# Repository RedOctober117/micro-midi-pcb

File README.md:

This repository contains the PCB for [micro-midi](https://github.com/RedOctober117/micro-midi).

## Dependencies
 - [scottokeebs](https://github.com/joe-scotto/scottokeebs)

## Examples

Outdated:

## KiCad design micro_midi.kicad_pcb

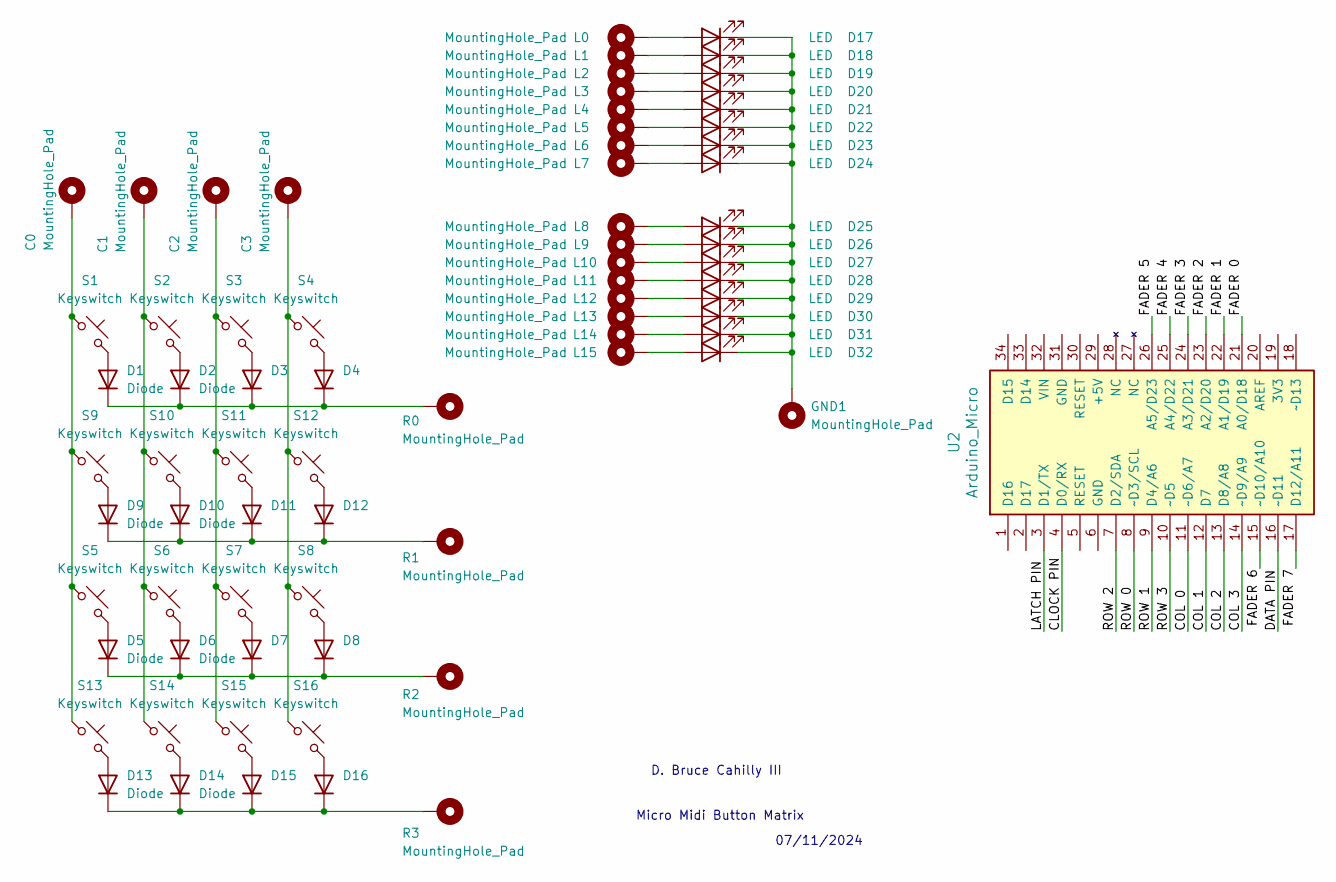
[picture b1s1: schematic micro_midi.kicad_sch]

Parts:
C0, C1, C2, C3: MountingHole_Pad; THROUGH HOLE PAD 1.7MM HOLE 3.0MM PAD
D1, D2, D3, D4, D5, D6, D7, D8, D9, D10, D11, D12, D13, D14, D15, D16: Diode; Diode_DO-35
D17, D18, D19, D20, D21, D22, D23, D24, D25, D26, D27, D28, D29, D30, D31, D32: LED; LED_D3.0mm
GND1: MountingHole_Pad; THROUGH HOLE PAD 1.7MM HOLE 3.0MM PAD
L0, L1, L2, L3, L4, L5, L6, L7, L8, L9, L10, L11, L12, L13, L14, L15: MountingHole_Pad; THROUGH HOLE PAD 1.7MM HOLE 3.0MM PAD
R0, R1, R2, R3: MountingHole_Pad; THROUGH HOLE PAD 1.7MM HOLE 3.0MM PAD
S1, S2, S3, S4, S5, S6, S7, S8, S9, S10, S11, S12, S13, S14, S15, S16: Keyswitch; MX_PCB_1.00u
U2: Arduino_Micro

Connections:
unnamed: C0.1, S1.1, S5.1, S9.1, S13.1
unnamed: C1.1, S2.1, S6.1, S10.1, S14.1
unnamed: C2.1, S3.1, S7.1, S11.1, S15.1
unnamed: C3.1, S4.1, S8.1, S12.1, S16.1
unnamed: D1.2 (A), S1.2
unnamed: D1.1 (K), D2.1 (K), D3.1 (K), D4.1 (K), R0.1
unnamed: D2.2 (A), S2.2
unnamed: D3.2 (A), S3.2
unnamed: D4.2 (A), S4.2
unnamed: D5.2 (A), S5.2
unnamed: D5.1 (K), D6.1 (K), D7.1 (K), D8.1 (K), R2.1
unnamed: D6.2 (A), S6.2
unnamed: D7.2 (A), S7.2
unnamed: D8.2 (A), S8.2
unnamed: D9.2 (A), S9.2
unnamed: D10.2 (A), S10.2
unnamed: D9.1 (K), D10.1 (K), D11.1 (K), D12.1 (K), R1.1
unnamed: D11.2 (A), S11.2
unnamed: D12.2 (A), S12.2
unnamed: D13.2 (A), S13.2
unnamed: D13.1 (K), D14.1 (K), D15.1 (K), D16.1 (K), R3.1
unnamed: D14.2 (A), S14.2
unnamed: D15.2 (A), S15.2
unnamed: D16.2 (A), S16.2
unnamed: D17.2 (A), L0.1
unnamed: D17.1 (K), D18.1 (K), D19.1 (K), D20.1 (K), D21.1 (K), D22.1 (K), D23.1 (K), D24.1 (K), D25.1 (K), D26.1 (K), D27.1 (K), D28.1 (K), D29.1 (K), D30.1 (K), D31.1 (K), D32.1 (K), GND1.1
unnamed: D18.2 (A), L1.1
unnamed: D19.2 (A), L2.1
unnamed: D20.2 (A), L3.1
unnamed: D21.2 (A), L4.1
unnamed: D22.2 (A), L5.1
unnamed: D23.2 (A), L6.1
unnamed: D24.2 (A), L7.1
unnamed: D25.2 (A), L8.1
unnamed: D26.2 (A), L9.1
unnamed: D27.2 (A), L10.1
unnamed: D28.2 (A), L11.1
unnamed: D29.2 (A), L12.1
unnamed: D30.2 (A), L13.1
unnamed: D31.2 (A), L14.1
unnamed: D32.2 (A), L15.1

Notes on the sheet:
07/11/2024
Micro Midi Button Matrix
D. Bruce Cahilly III

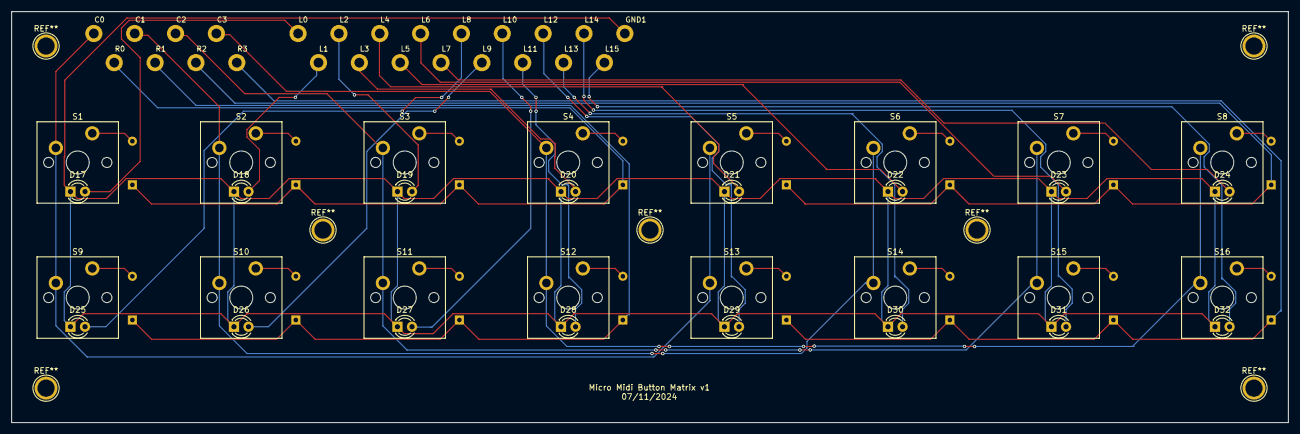
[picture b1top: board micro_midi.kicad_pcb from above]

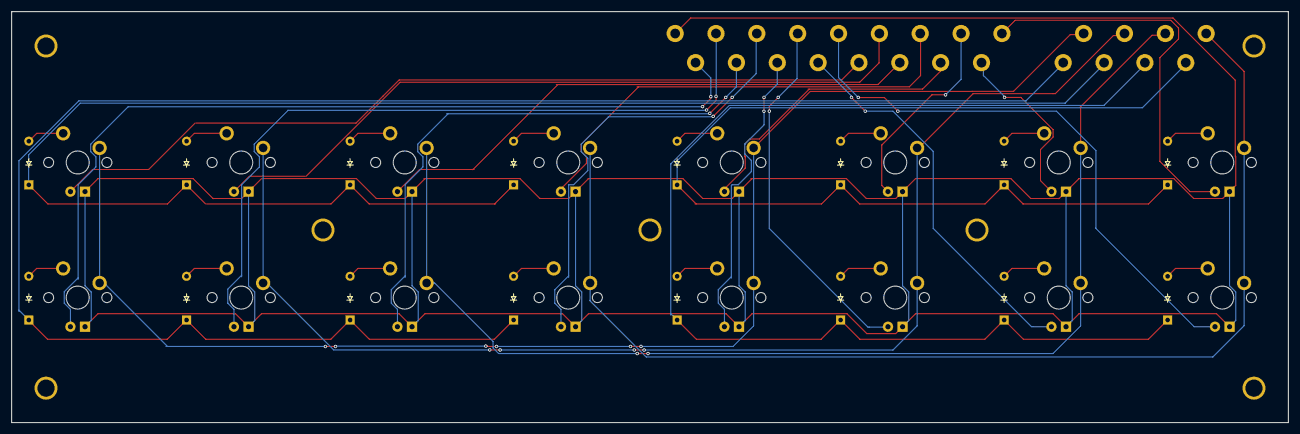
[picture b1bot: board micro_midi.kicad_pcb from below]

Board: 2 copper layers, 222.5 x 71.6 mm, 73 parts (16 on the bottom side), 41 nets.

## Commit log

2024-10-31 init
2024-10-31 added readme
2024-11-02 resistor change and pdf
2024-11-04 nearing completion
2024-11-04 made svg
2024-11-04 updated screw positions
2024-11-05 zip and misc
2024-11-07 screw holes and smaller footprint
2024-11-07 cleaned repo and readme
2024-11-08 reaaligned
2024-12-02 in progress
2024-12-09 finalized realign of buttons; no work on faders
2024-12-09 cleanup
2024-12-09 new step
